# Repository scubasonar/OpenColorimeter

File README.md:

# OpenColorimeter
Open source colorimeter project by Matthew Valancy for California State University Monterey Bay Capstone.

Hardware and software for measuring light passing through a sample vial.

*Mechanical design in FreeCAD v0.17
*Electrical design in KiCAD 5.0.0
*Software written with Arduino IDE 1.8.7

### See Wiki for more information.

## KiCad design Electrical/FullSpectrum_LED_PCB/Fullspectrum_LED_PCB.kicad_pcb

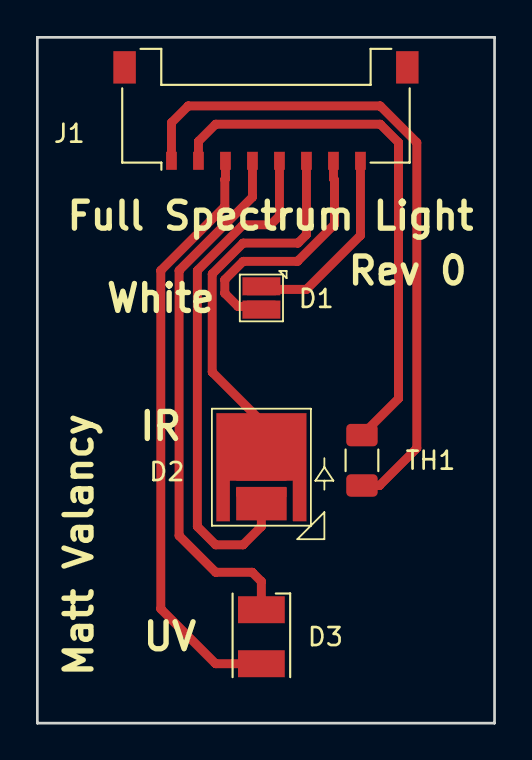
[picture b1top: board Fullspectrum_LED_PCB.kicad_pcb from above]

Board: 2 copper layers, 25.4 x 38.1 mm, 5 parts (0 on the bottom side), 8 nets.

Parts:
D1: White_LED; LED_Cree_XQ-E
D2: IR_LED; LED_Oslon_SFH_4735
D3: UV_LED; LED_PLCC-2
J1: Conn_01x08_Male; Molex_Pico-Lock_504050-0891_1x08-1MP_P1.50mm_Horizontal
TH1: Thermistor_NTC; R_1206_3216Metric

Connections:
unnamed: D1.1, J1.8
unnamed: D1.2, J1.7
unnamed: D2.1, J1.6
unnamed: D2.2, J1.5
unnamed: D3.1, J1.4
unnamed: D3.2, J1.3
unnamed: J1.1, TH1.1
unnamed: J1.2, TH1.2

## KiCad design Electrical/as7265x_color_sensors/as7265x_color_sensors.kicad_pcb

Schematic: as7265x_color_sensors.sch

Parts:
C1, C2, C3: 100nF; C_0805_2012Metric
C4, C5, C6: 10uF; C_0805_2012Metric
C7: 1uF; C_0805_2012Metric
D1, D2, D3, D4, D5, D6: LED_Small; LED_1206_3216Metric
F1, F2: Polyfuse; C_1206_3216Metric
J1: Conn_01x06_Male; Harwin_M20-89006xx_1x06_P2.54mm_Horizontal
J2, J3: RJ12; RJ12_Amphenol_54601
R1, R2, R3, R4, R5, R6: R_Small; R_0805_2012Metric
R7: 10k; R_0805_2012Metric
R8: DNP; R_0805_2012Metric
R9: 0R; R_0805_2012Metric
R10, R11, R12, R13: 10K; R_0805_2012Metric
TP1, TP2, TP3, TP4, TP5, TP6, TP8, TP9, TP10, TP11, TP12, TP13, TP14, TP15, TP17: TestPoint; Pin_D1.0mm_L10.0mm_LooseFit
TVS1, TVS2, TVS3: SP3012-06UTG; uDFN-14_3.5x1.35x0.5mm
U1: AS72651; LGA-20_4.5mm_4.7mm_2.5mm
U2: AS72652; LGA-20_4.5mm_4.7mm_2.5mm
U3: AS72653; LGA-20_4.5mm_4.7mm_2.5mm
U4: AT25SF041; SOIC-8_3.9x4.9mm_P1.27mm

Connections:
+3V3: C1.1, C2.1, C3.1, C4.1, C5.1, C6.1, C7.1, F1.1, F2.1, J1.4, R1.2, R2.2, R3.2, R4.2, R5.2, R6.2, R7.1, R8.2, TP1.1, TP14.1, TVS1.13, TVS2.13, TVS3.9, U1.14, U1.17, U2.14, U2.17, U3.14, U3.17, U4.3 (~WP), U4.7 (~HOLD), U4.8 (VCC)
/CTS: J1.5, TP15.1, TVS3.8
/DTR: J1.1, TP11.1, TVS3.13
/LED1: D1.1, J3.2, TVS2.8, U1.18
/LED2: D2.1, J3.3, TVS2.9, U1.15
/LED3: D3.1, J3.4, TVS2.11, U2.18
/LED4: D4.1, J3.5, TVS2.12, U2.15
/LED5: D5.1, J2.2, TVS1.8, U3.18
/LED6: D6.1, J2.3, TVS1.9, U3.15
/RXI: J1.3, J2.4, TP13.1, TVS1.11, TVS3.11, U1.11
/TXO: J1.2, J2.5, TP12.1, TVS1.12, TVS3.12, U1.12
/~INT: TP17.1, U1.13
GND: C1.2, C2.2, C3.2, C4.2, C5.2, C6.2, C7.2, J1.6, J2.1, J3.1, R9.1, R10.1, R11.1, R12.1, R13.1, TVS1.10, TVS2.10, TVS3.10, U1.16, U2.16, U3.16, U4.4 (GND)
unnamed: D1.2, R1.1
unnamed: D2.2, R2.1
unnamed: D3.2, R3.1
unnamed: D4.2, R4.1
unnamed: D5.2, R5.1
unnamed: D6.2, R6.1
unnamed: F1.2, J2.6
unnamed: F2.2, J3.6
unnamed: R7.2, U1.2, U2.2, U3.2
unnamed: R8.1, R9.2, TP5.1, U1.8
unnamed: R10.2, U3.5
unnamed: R11.2, U2.5
unnamed: R12.2, U3.7
unnamed: R13.2, U2.7
unnamed: TP2.1, U1.10, U2.10, U3.10
unnamed: TP3.1, U1.9, U2.9, U3.9
unnamed: TP4.1, U1.7
unnamed: TP6.1, U1.6, U4.1 (~CS)
unnamed: TP8.1, U1.5, U4.2 (MISO)
unnamed: TP9.1, U1.4, U4.5 (MOSI)
unnamed: TP10.1, U1.3, U4.6 (SCK)

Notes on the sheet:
Connector for SparkFun FTDI Basic Breakout - 3.3V
LED port
Comm port
Firmware
Master Color Sensor
Expansion Color Sensor
FTDI Plug

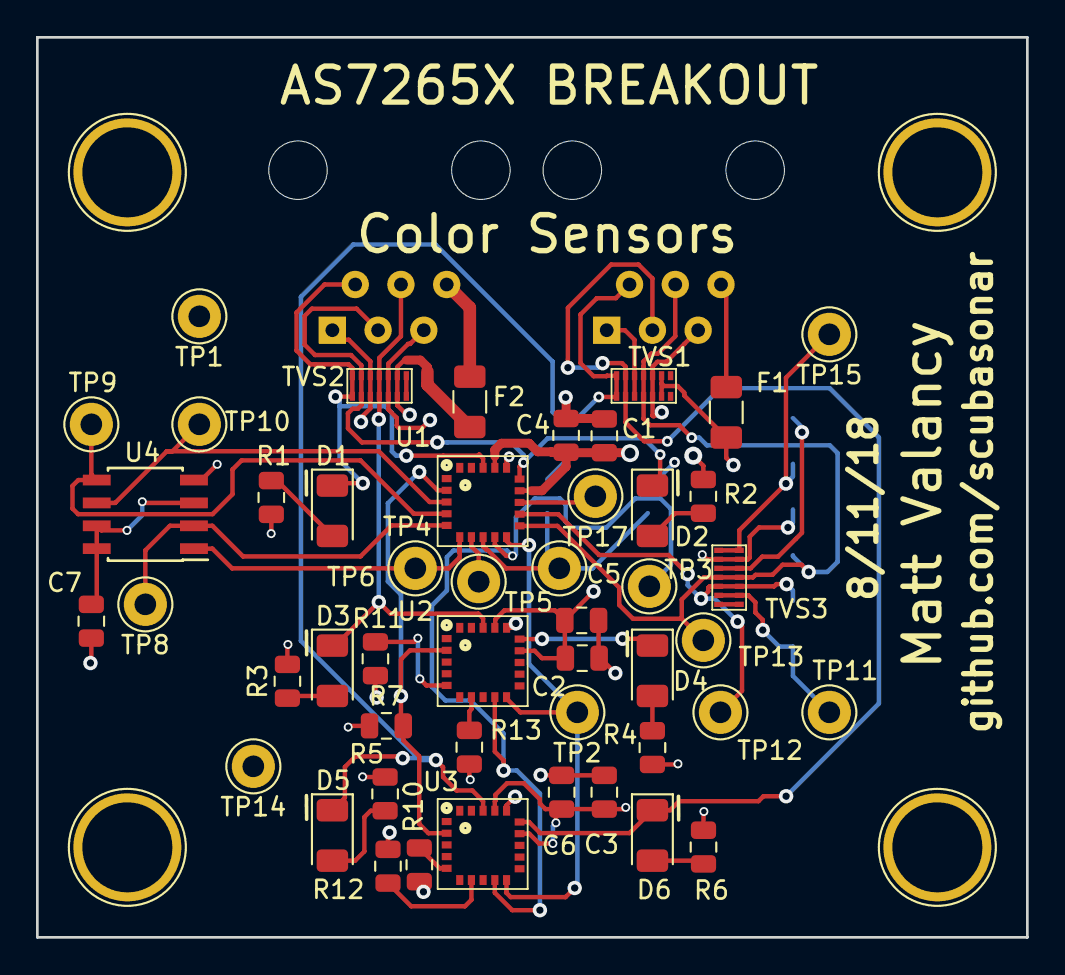
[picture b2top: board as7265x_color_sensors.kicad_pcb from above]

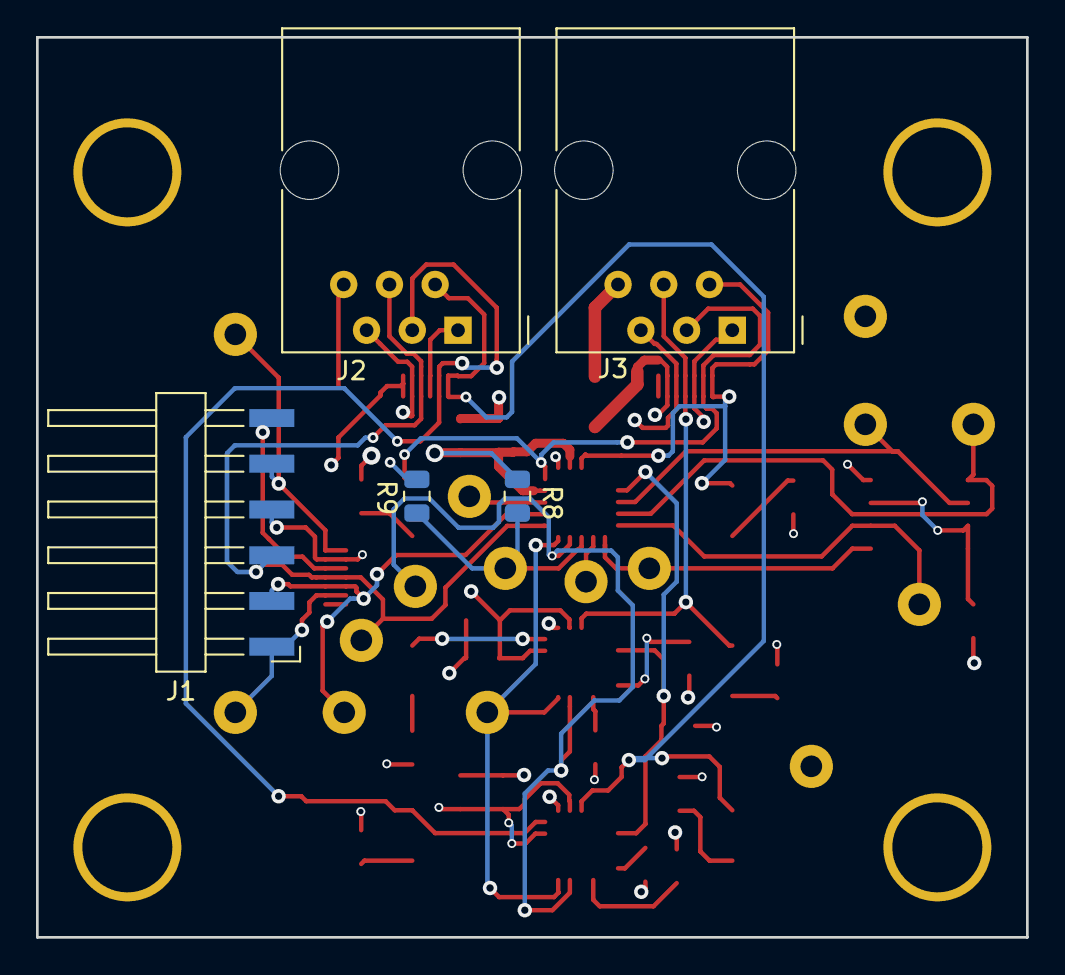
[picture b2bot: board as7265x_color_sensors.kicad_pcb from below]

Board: 4 copper layers, 55.0 x 50.0 mm, 53 parts (5 on the bottom side), 34 nets.

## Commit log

2018-07-29 start of project
2018-07-29 added LICENSE.md
2018-07-30 added some basic CAD concept
2018-09-25 added software
2018-09-25 added new files
2018-09-27 designed new light source for spectrometry with full range of light 400nm-1050nm
2018-10-01 worked on mechanical housing, printing new version overnight
2018-10-01 added color sensor board
2018-10-01 moved light pcb out of unnecessary folder
2018-10-02 shifted sensor board position for light alignment and tightened up the test tube holder
2018-10-04 made first version of lid, printing test part now
